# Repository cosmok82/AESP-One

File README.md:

# AESP-One
<div style="text-align: center;">

</div>
<br>
Author: Cosimo Orlando.<br>
Blog: http://creativityslashdesign.com/<br>
<br>
Fully compatible ESP8266 development board<br>
<br>
These files are released under a Creative Commons Attribution for Non Commercial use (author apart) Share-Alike (CC BY-NC-SA).

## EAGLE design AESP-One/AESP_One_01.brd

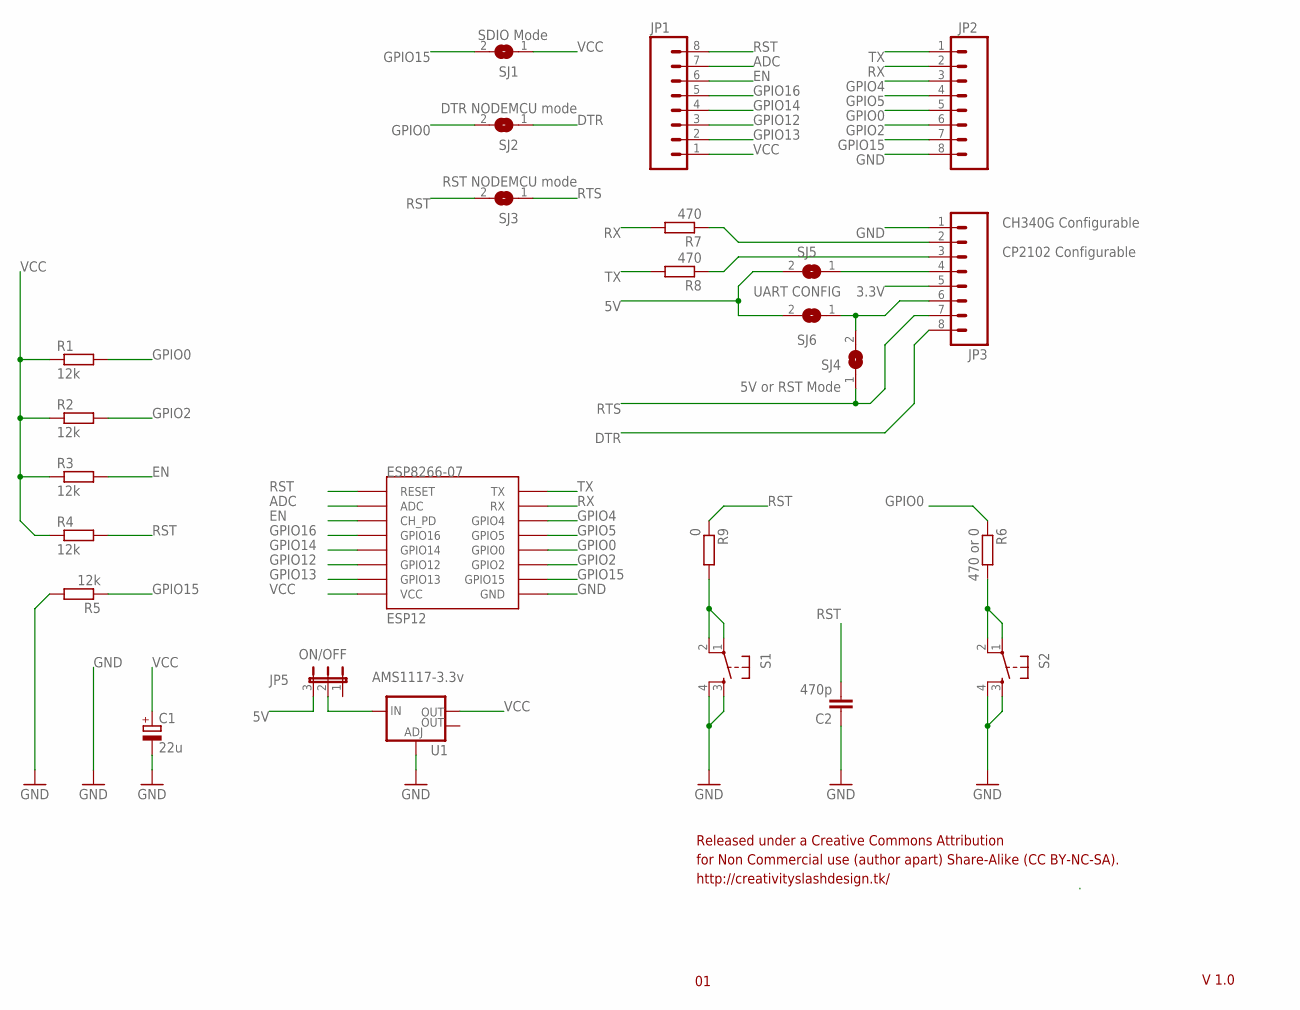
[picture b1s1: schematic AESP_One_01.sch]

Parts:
C1: 22u; 140CLH-0810
C2: 470p; C0805
ESP8266-07: ESP12
JP1, JP2, JP3: M08LONGPADS; 1X08_LONGPADS
JP5: ON/OFF; JP2W
R1, R2, R3, R4, R5: 12k; M0805
R6: 470 or 0; M0805
R7, R8: 470; M0805
R9: 0; M0805
S1, S2: TAC_SWITCHSMD; TACTILE-SWITCH-SMD
SJ1: SDIO Mode; SJ
SJ2: DTR NODEMCU mode; SJ
SJ3: RST NODEMCU mode; SJ
SJ4: 5V or RST Mode; SJ
SJ5, SJ6: SJ
U1: AMS1117-3.3v; SOT223

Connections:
3.3V: JP3.5
5V: JP5.3, SJ5.2, SJ6.2
ADC: ESP8266-07.ADC, JP1.7
DTR: JP3.8, SJ2.1
EN: ESP8266-07.CH_PD, JP1.6, R3.2
GND: C1.-, C2.1, ESP8266-07.GND, JP2.8, JP3.1, R5.2, S1.3, S1.4, S2.3, S2.4, U1.1 (ADJ)
GPIO0: ESP8266-07.GPIO0, JP2.5, R1.2, R6.1, SJ2.2
GPIO2: ESP8266-07.GPIO2, JP2.6, R2.2
GPIO4: ESP8266-07.GPIO4, JP2.3
GPIO5: ESP8266-07.GPIO5, JP2.4
GPIO12: ESP8266-07.GPIO12, JP1.3
GPIO13: ESP8266-07.GPIO13, JP1.2
GPIO14: ESP8266-07.GPIO14, JP1.4
GPIO15: ESP8266-07.GPIO15, JP2.7, R5.1, SJ1.2
GPIO16: ESP8266-07.GPIO16, JP1.5
unnamed: R6.2, S2.1, S2.2
unnamed: R9.2, S1.1, S1.2
unnamed: JP3.3, R8.1
unnamed: JP5.2, U1.3 (IN)
unnamed: JP3.4, SJ5.1
unnamed: JP3.6, SJ4.2, SJ6.1
unnamed: JP3.2, R7.1
RST: C2.2, ESP8266-07.RESET, JP1.8, R4.2, R9.1, SJ3.2
RTS: JP3.7, SJ3.1, SJ4.1
RX: ESP8266-07.RX, JP2.2, R7.2
TX: ESP8266-07.TX, JP2.1, R8.2
VCC: C1.+, ESP8266-07.VCC, JP1.1, R1.1, R2.1, R3.1, R4.1, SJ1.1, U1.2 (OUT)

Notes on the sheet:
CH340G Configurable
CP2102 Configurable
UART CONFIG
Released under a Creative Commons Attribution
for Non Commercial use (author apart) Share-Alike (CC BY-NC-SA).
http://creativityslashdesign.tk/
V 1.0

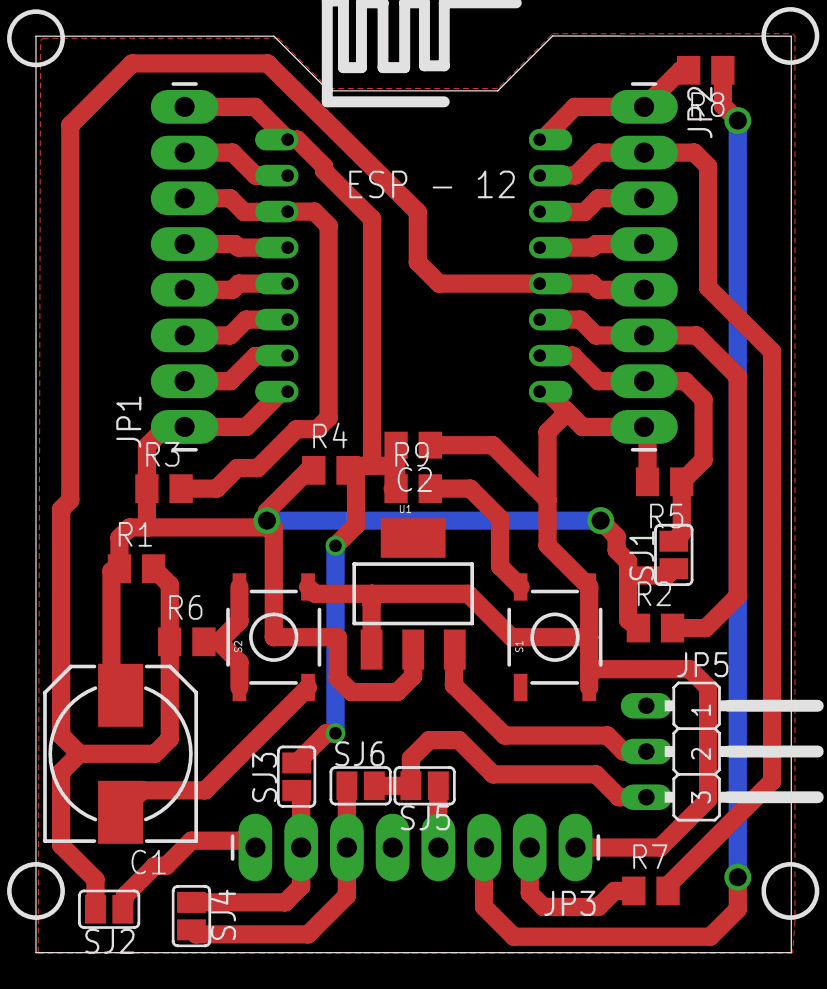
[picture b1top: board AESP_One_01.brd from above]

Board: 2 copper layers, 42.0 x 50.9 mm, 25 parts (0 on the bottom side), 26 nets.

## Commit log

2015-07-01 first release
2019-09-20 Update README.md
    com update

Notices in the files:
parts and their libraries:
SparkFun-Connectors: Licensing: Creative Commons ShareAlike 4.0 International - https://creativecommons.org/licenses/by-sa/4.0
